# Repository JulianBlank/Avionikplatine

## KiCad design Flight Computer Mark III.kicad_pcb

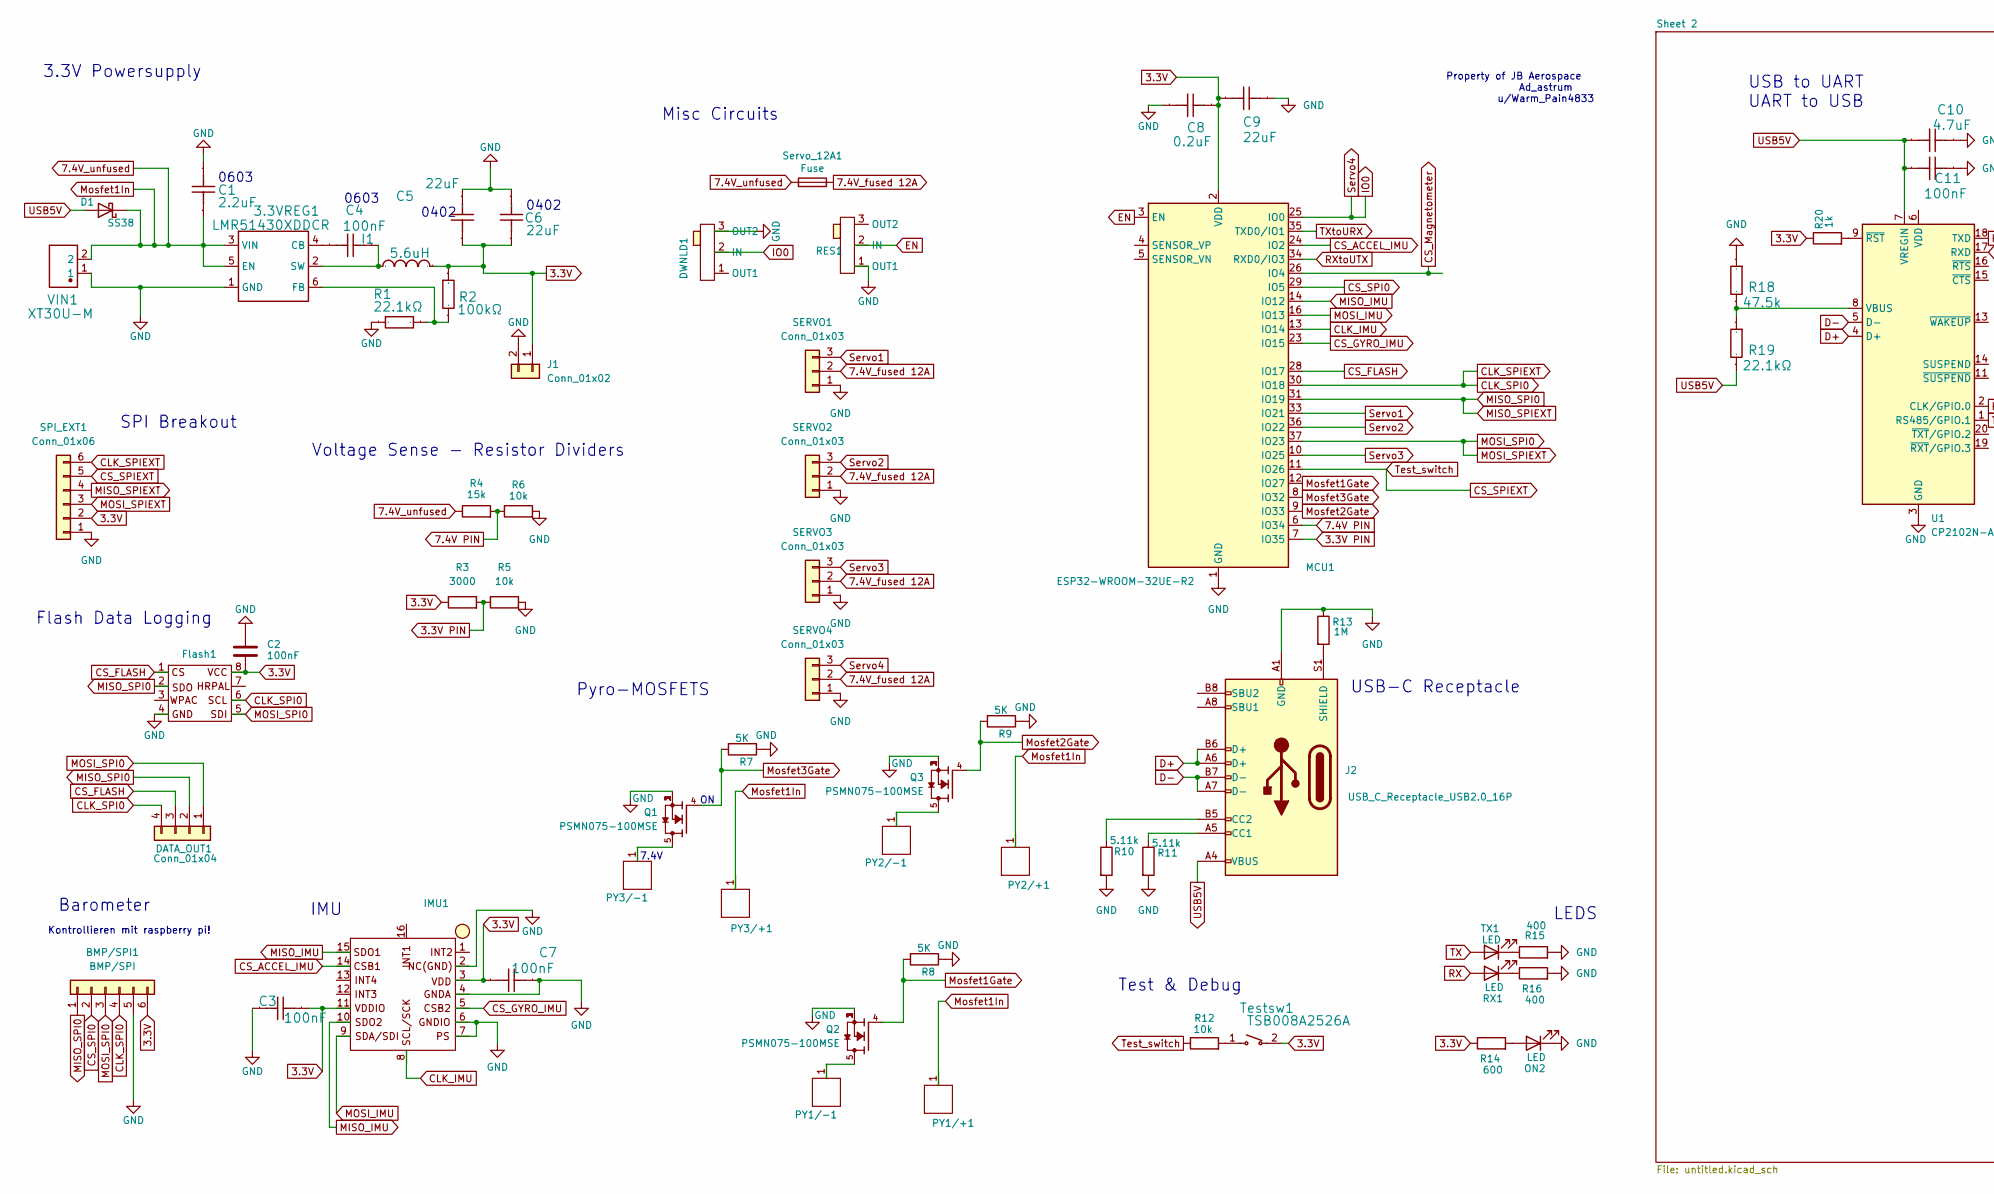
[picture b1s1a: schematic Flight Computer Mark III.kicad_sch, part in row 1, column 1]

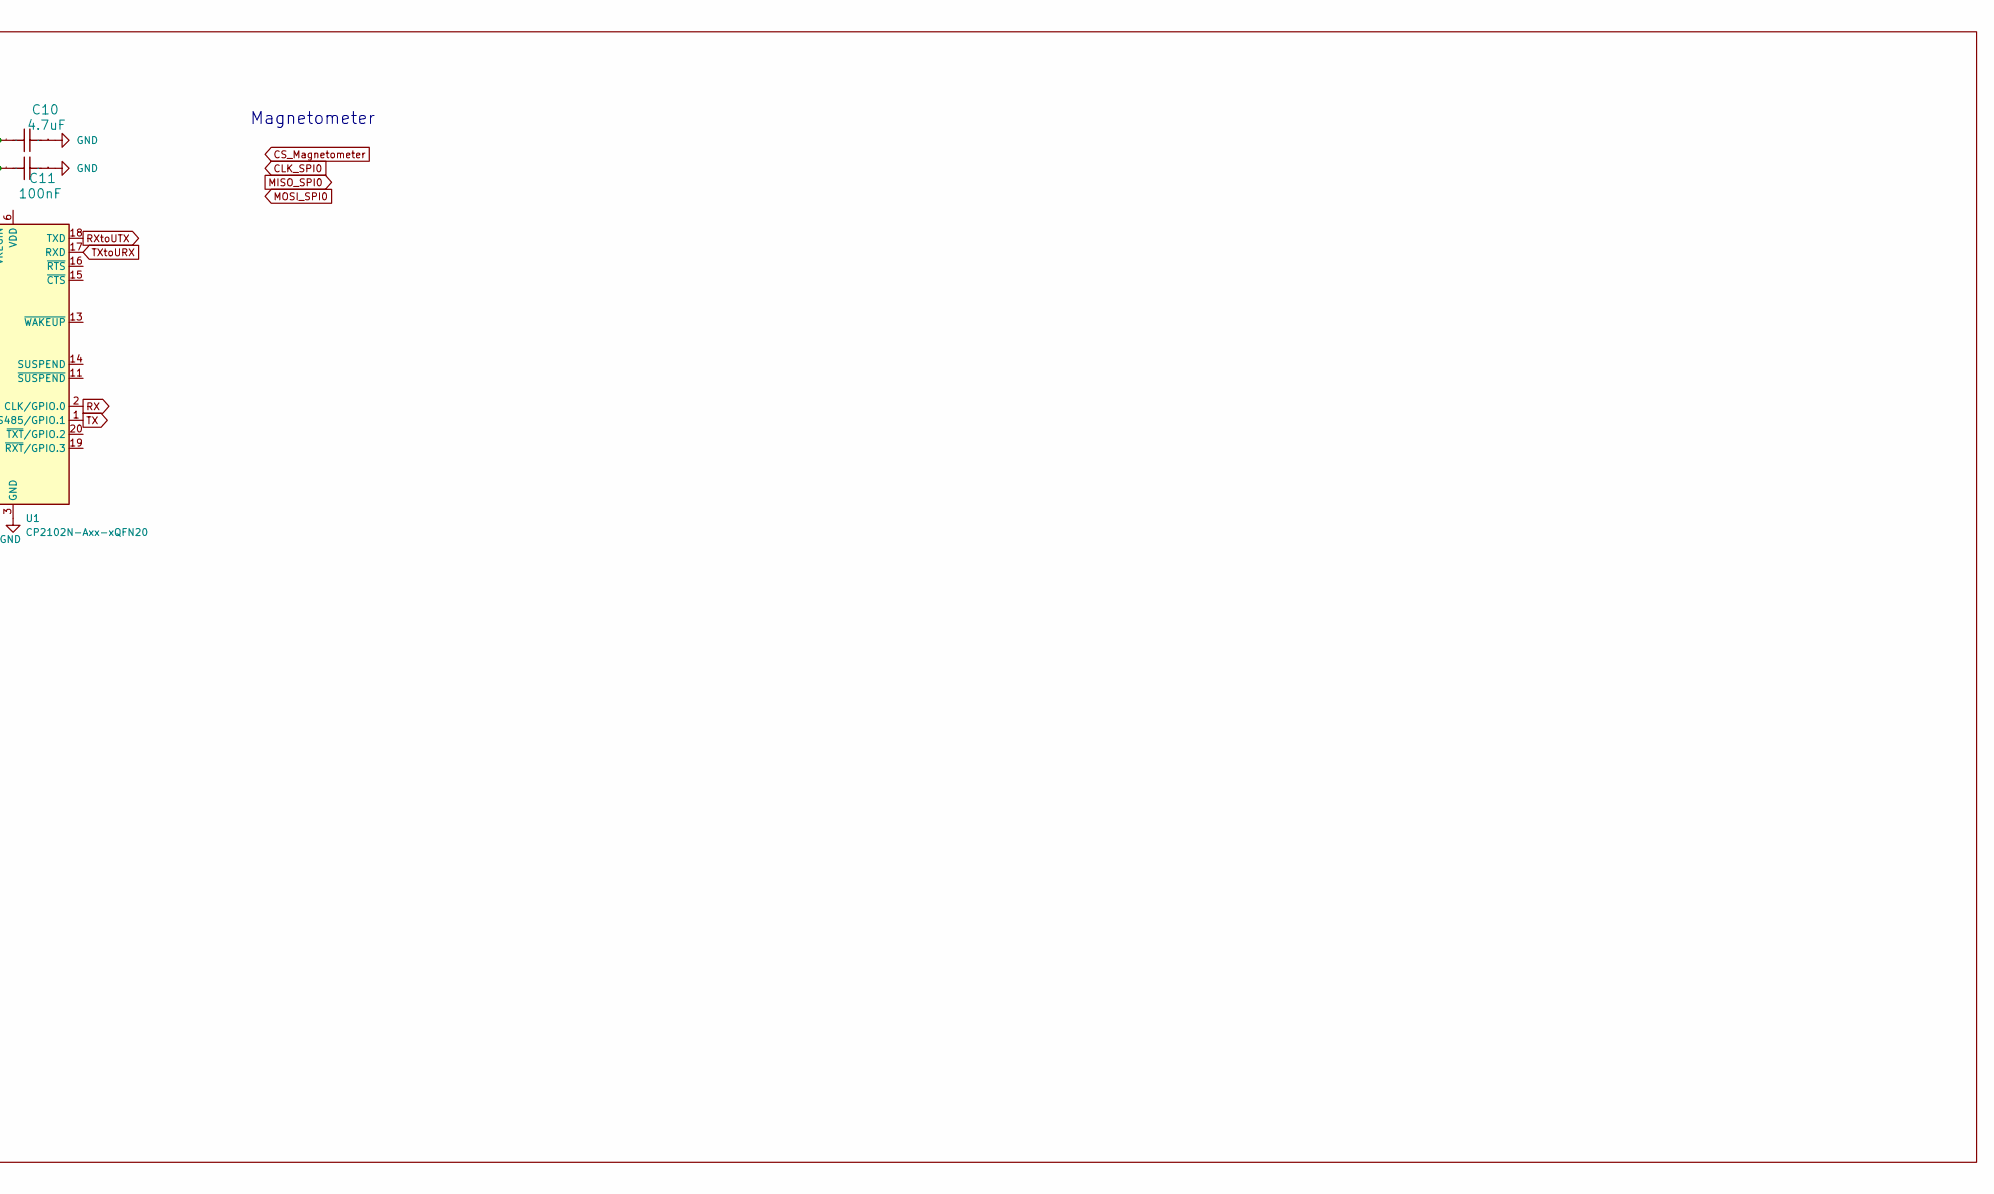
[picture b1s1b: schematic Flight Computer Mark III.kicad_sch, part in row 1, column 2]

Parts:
3.3VREG1: LMR51430XDDCR; LMR41430XDDCR; Manufacturer Part LMR51430XDDCR
BMP/SPI1: BMP/SPI; PinHeader_1x06_P2.54mm_Vertical
C1: 2.2uF; C_0603_1608Metric; Manufacturer Part CC0603KRX7R6BB225
C2: 100nF; C_0603_1608Metric
C3, C4, C7, C11: 100nF; C_0603_1608Metric; Manufacturer Part CC0402KRX7R7BB104
C5, C6, C9: 22uF; C_0603_1608Metric; Manufacturer Part CGA0402X5R226M100GT
C8: 0.2uF; C_0603_1608Metric; Manufacturer Part CGA0402X5R226M100GT
C10: 4.7uF; C_0402_1005Metric; Manufacturer Part CC0402KRX7R7BB104
D1: SS38; D_SMA
DATA_OUT1: Conn_01x04; B4B-ZR-S
DWNLD1: SS12D00G3
Flash1: MX25L25645G
I1: 5.6uH; YSPI0520-5R6M; Manufacturer Part YSPI0520-5R6M
IMU1: BMI088
J1: Conn_01x02; PinHeader_1x02_P2.54mm_Vertical
J2: USB_C_Receptacle_USB2.0_16P; USB_C_Receptacle_GCT_USB4105-xx-A_16P_TopMnt_Horizontal
MCU1: ESP32-WROOM-32UE-R2; ESP32-WROOM-32UE
ON2: LED; LED_0805_2012Metric
PY1/+1, PY1/-1, PY2/+1, PY2/-1, PY3/+1, PY3/-1: Pyro_pad
Q1, Q2, Q3: PSMN075-100MSE; LFPAK33; PARTREV 24 July 2024
R1, R19: 22.1kΩ; R_0603_1608Metric; Manufacturer Part 0603WAF2212T5E
R2: 100kΩ; R_0603_1608Metric; Manufacturer Part RC0402FR-07100KL
R3: 3000; R_0603_1608Metric
R4: 15k; R_0603_1608Metric
R5, R6, R12: 10k; R_0603_1608Metric
R7, R8, R9: 5K; R_0603_1608Metric
R10, R11: 5.11k; R_0402_1005Metric_Pad0.72x0.64mm_HandSolder
R13: 1M; R_0402_1005Metric_Pad0.72x0.64mm_HandSolder
R14: 600; R_0603_1608Metric
R15, R16: 400; R_0603_1608Metric
R18: 47.5k; R_0402_1005Metric; Manufacturer Part 0603WAF2212T5E
R20: 1k; R_0402_1005Metric_Pad0.72x0.64mm_HandSolder
RES1: SS12D00G3
RX1: LED; LED_0805_2012Metric
SERVO1, SERVO2, SERVO3, SERVO4: Conn_01x03; PinHeader_1x03_P2.54mm_Vertical
SPI_EXT1: Conn_01x06; B6B-ZR-T
Servo_12A1: Fuse; Fuse_1206_3216Metric_Pad1.42x1.75mm_HandSolder
TX1: LED; LED_0805_2012Metric
Testsw1: TSB008A2526A; TSB008; Manufacturer Part TSB008A2526A
U1: CP2102N-Axx-xQFN20; SiliconLabs_QFN-20-1EP_3x3mm_P0.5mm_EP1.8x1.8mm
VIN1: XT30U-M; AMASS_XT30U-F_1x02_P5.0mm_Vertical; Manufacturer Part XT30U-M

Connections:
3.3V: BMP/SPI1.6, C2.2, C3.2, C5.2, C6.2, C7.2, C8.1, C9.2, Flash1.8, I1.2, IMU1.3, IMU1.11, J1.1, MCU1.2 (VDD), R2.1, R3.1, R14.1, R20.1, SPI_EXT1.2, Testsw1.2
3.3V PIN: MCU1.7 (IO35), R3.2, R5.1
7.4V PIN: MCU1.6 (IO34), R4.2, R6.1
7.4V_fused 12A: SERVO1.2, SERVO2.2, SERVO3.2, SERVO4.2, Servo_12A1.2
7.4V_unfused: 3.3VREG1.3 (VIN), 3.3VREG1.5 (EN), C1.1, D1.1 (K), PY1/+1.1, PY2/+1.1, PY3/+1.1, R4.1, Servo_12A1.1, VIN1.2
CLK_IMU: IMU1.8, MCU1.13 (IO14)
CLK_SPI0: BMP/SPI1.4, DATA_OUT1.4, Flash1.6, MCU1.30 (IO18), SPI_EXT1.6
CS_ACCEL_IMU: IMU1.14, MCU1.24 (IO2)
CS_FLASH: DATA_OUT1.3, Flash1.1, MCU1.28 (IO17)
CS_GYRO_IMU: IMU1.5, MCU1.23 (IO15)
CS_Magnetometer: MCU1.26 (IO4)
CS_SPI0: BMP/SPI1.2, MCU1.29 (IO5)
CS_SPIEXT: MCU1.11 (IO26), R12.1, SPI_EXT1.5
D+: J2.A6 (D+), J2.B6 (D+), U1.4 (D+)
D-: J2.A7 (D-), J2.B7 (D-), U1.5 (D-)
EN: MCU1.3 (EN), RES1.2 (IN)
GND: 3.3VREG1.1 (GND), BMP/SPI1.5, C1.2, C2.1, C3.1, C5.1, C6.1, C7.1, C8.2, C9.1, C10.1, C11.1, DWNLD1.3 (OUT2), Flash1.4, IMU1.2, IMU1.4, IMU1.6, IMU1.7, J1.2, J2.A1 (GND), J2.A12 (GND), J2.B1 (GND), J2.B12 (GND), MCU1.1 (GND), MCU1.15 (GND), MCU1.38 (GND), MCU1.39 (GND), ON2.1 (K), Q1.1, Q1.2, Q1.3, Q2.1, Q2.2, Q2.3, Q3.1, Q3.2, Q3.3, R1.2, R5.2, R6.2, R7.1, R8.1, R9.1, R10.2, R11.2, R13.1, R15.2, R16.2, R18.2, RES1.1 (OUT1), SERVO1.1, SERVO2.1, SERVO3.1, SERVO4.1, SPI_EXT1.1, U1.3 (GND), U1.12 (GND), U1.21 (GND), VIN1.1
IO0: DWNLD1.2 (IN), MCU1.25 (IO0), SERVO4.3
MISO_IMU: IMU1.10, IMU1.15, MCU1.14 (IO12)
MISO_SPI0: BMP/SPI1.1, DATA_OUT1.2, Flash1.2, MCU1.31 (IO19), SPI_EXT1.4
MOSI_IMU: IMU1.9, MCU1.16 (IO13)
MOSI_SPI0: BMP/SPI1.3, DATA_OUT1.1, Flash1.5, MCU1.37 (IO23), SPI_EXT1.3
Mosfet1Gate: MCU1.12 (IO27), Q2.4, R8.2
Mosfet2Gate: MCU1.9 (IO33), Q3.4, R9.2
Mosfet3Gate: MCU1.8 (IO32), Q1.4, R7.2
unnamed: 3.3VREG1.4 (CB), C4.1
unnamed: 3.3VREG1.6 (FB), R1.1, R2.2
unnamed: 3.3VREG1.2 (SW), C4.2, I1.1
unnamed: J2.A5 (CC1), R11.1
unnamed: J2.B5 (CC2), R10.1
unnamed: J2.S1 (SHIELD), R13.2
unnamed: ON2.2 (A), R14.2
unnamed: PY1/-1.1, Q2.5
unnamed: PY2/-1.1, Q3.5
unnamed: PY3/-1.1, Q1.5
unnamed: R12.2, Testsw1.1
unnamed: R16.1, RX1.1 (K)
unnamed: R15.1, TX1.1 (K)
unnamed: R18.1, R19.2, U1.8 (VBUS)
unnamed: R20.2, U1.9 (~RST)
RX: RX1.2 (A), U1.2 (CLK/GPIO.0)
RXtoUTX: MCU1.34 (RXD0/IO3), U1.18 (TXD)
Servo1: MCU1.33 (IO21), SERVO1.3
Servo2: MCU1.36 (IO22), SERVO2.3
Servo3: MCU1.10 (IO25), SERVO3.3
TX: TX1.2 (A), U1.1 (RS485/GPIO.1)
TXtoURX: MCU1.35 (TXD0/IO1), U1.17 (RXD)
USB5V: C10.2, C11.2, D1.2 (A), J2.A4 (VBUS), J2.A9 (VBUS), J2.B4 (VBUS), J2.B9 (VBUS), R19.1, U1.7 (VREGIN)

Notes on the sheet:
0402
Kontrollieren mit raspberry pi!
USB-C Receptacle
Test & Debug
IMU
SPI Breakout
Barometer
USB to UART UART to USB
0603
7.4V
Voltage Sense - Resistor Dividers
Misc Circuits
Flash Data Logging
3.3V Powersupply
Property of JB Aerospace Ad_astrum u/Warm_Pain4833
0603
Pyro-MOSFETS
LEDS
Magnetometer

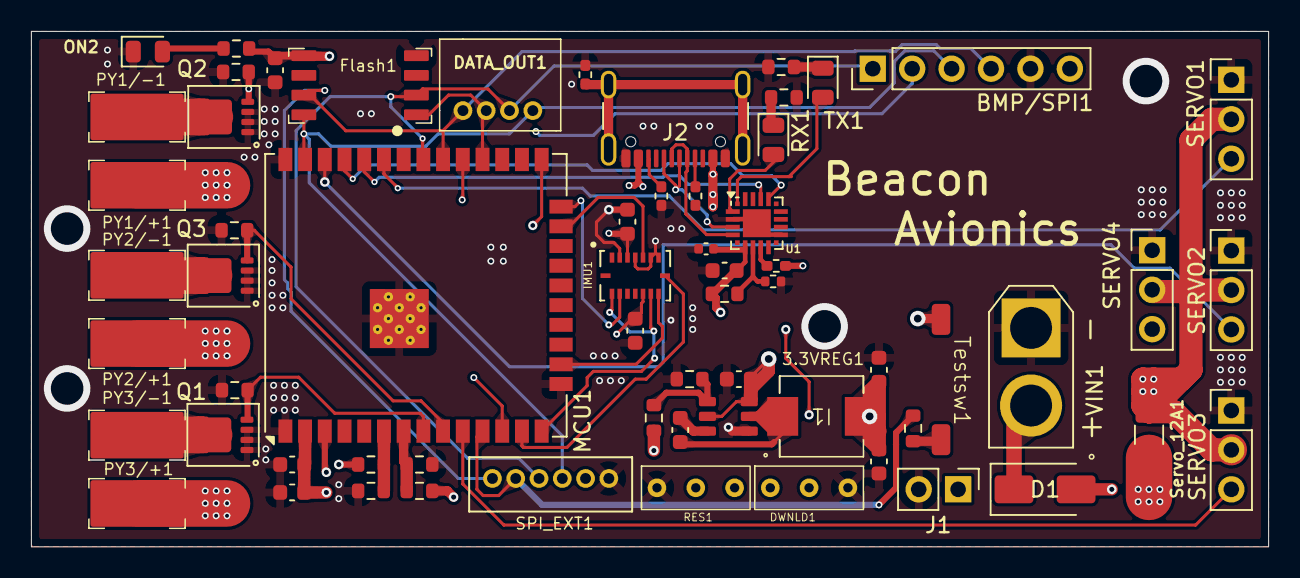
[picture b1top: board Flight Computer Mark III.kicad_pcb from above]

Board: 4 copper layers, 79.7 x 33.2 mm, 63 parts (0 on the bottom side), 47 nets.

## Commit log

2025-05-25 Added 3d models
2025-05-25 Changed some via diameters, added 3D models, restructured the GND planes
2025-05-26 Added GND vias, changed some via sizes
2025-05-26 Finished Layout, TODO: DRM check
2025-05-27 changed via diamters according to DRC requirements
